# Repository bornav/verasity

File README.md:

# Verasity

Open source tenkeyless keyboard

* Keyboard Maintainer: [Borna Vincek](https://github.com/BornaV)

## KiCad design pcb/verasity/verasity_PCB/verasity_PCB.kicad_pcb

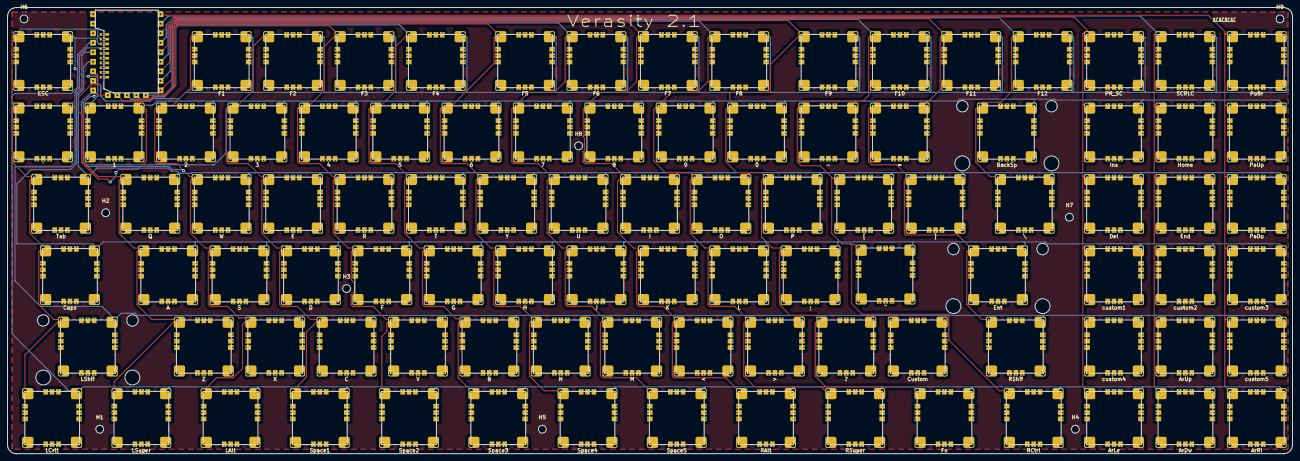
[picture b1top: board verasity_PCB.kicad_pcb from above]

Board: 2 copper layers, 342.9 x 119.1 mm, 107 parts (0 on the bottom side), 23 nets.

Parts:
H1, H2, H3, H4, H5, H6, H7, H8, H9: MountingHole_Pad; MountingHole_2.1mm
U2: ESC; inverse_socket_MX_hotswap
U3: custom1; inverse_socket_MX_hotswap
U4: F1; inverse_socket_MX_hotswap
U5: F2; inverse_socket_MX_hotswap
U6: F3; inverse_socket_MX_hotswap
U7: F4; inverse_socket_MX_hotswap
U8: F5; inverse_socket_MX_hotswap
U9: F6; inverse_socket_MX_hotswap
U10: F7; inverse_socket_MX_hotswap
U11: F8; inverse_socket_MX_hotswap
U12: F9; inverse_socket_MX_hotswap
U13: F10; inverse_socket_MX_hotswap
U14: F11; inverse_socket_MX_hotswap
U15: F12; inverse_socket_MX_hotswap
U16: PR_SC; inverse_socket_MX_hotswap
U17: SCRLC; inverse_socket_MX_hotswap
U18: PoBr; inverse_socket_MX_hotswap
U19: `; inverse_socket_MX_hotswap
U20: 1; inverse_socket_MX_hotswap
U21: 2; inverse_socket_MX_hotswap
U22: 3; inverse_socket_MX_hotswap
U23: 4; inverse_socket_MX_hotswap
U24: 5; inverse_socket_MX_hotswap
U25: 6; inverse_socket_MX_hotswap
U26: 7; inverse_socket_MX_hotswap
U27: 8; inverse_socket_MX_hotswap
U28: 9; inverse_socket_MX_hotswap
U29: 0; inverse_socket_MX_hotswap
U30: -; inverse_socket_MX_hotswap
U31: =; inverse_socket_MX_hotswap
U32: BackSp; inverse_socket_MX_hotswap_2.5U_stabilizers
U33: Ins; inverse_socket_MX_hotswap
U34: Home; inverse_socket_MX_hotswap
U35: PaUp; inverse_socket_MX_hotswap
U36: Tab; inverse_socket_MX_hotswap
U37: Q; inverse_socket_MX_hotswap
U38: W; inverse_socket_MX_hotswap
U39: E; inverse_socket_MX_hotswap
U40: R; inverse_socket_MX_hotswap
U41: T; inverse_socket_MX_hotswap
U42: Y; inverse_socket_MX_hotswap
U43: U; inverse_socket_MX_hotswap
U44: I; inverse_socket_MX_hotswap
U45: O; inverse_socket_MX_hotswap
U46: P; inverse_socket_MX_hotswap
U47: [; inverse_socket_MX_hotswap
U48: ]; inverse_socket_MX_hotswap
U49: \; inverse_socket_MX_hotswap
U50: Del; inverse_socket_MX_hotswap
U51: End; inverse_socket_MX_hotswap
U52: PaDo; inverse_socket_MX_hotswap
U53: Caps; inverse_socket_MX_hotswap
U54: A; inverse_socket_MX_hotswap
U55: S; inverse_socket_MX_hotswap
U56: D; inverse_socket_MX_hotswap
U57: F; inverse_socket_MX_hotswap
U58: G; inverse_socket_MX_hotswap
U59: H; inverse_socket_MX_hotswap
U60: J; inverse_socket_MX_hotswap
U61: K; inverse_socket_MX_hotswap
U62: L; inverse_socket_MX_hotswap
U63: ;; inverse_socket_MX_hotswap
U64: "; inverse_socket_MX_hotswap
U65: Ent; inverse_socket_MX_hotswap_2.5U_stabilizers
U66: LShif; inverse_socket_MX_hotswap_2.5U_stabilizers
U67: Z; inverse_socket_MX_hotswap
U68: X; inverse_socket_MX_hotswap
U69: C; inverse_socket_MX_hotswap
U70: V; inverse_socket_MX_hotswap
U71: B; inverse_socket_MX_hotswap
U72: N; inverse_socket_MX_hotswap
U73: M; inverse_socket_MX_hotswap
U74: <; inverse_socket_MX_hotswap
U75: >; inverse_socket_MX_hotswap
U76: ?; inverse_socket_MX_hotswap
U77: Custom; inverse_socket_MX_hotswap
U78: RShif; inverse_socket_MX_hotswap
U79: ArUp; inverse_socket_MX_hotswap
U80: LCrtl; inverse_socket_MX_hotswap
U81: LSuper; inverse_socket_MX_hotswap
U82: LAlt; inverse_socket_MX_hotswap
U83: Space1; inverse_socket_MX_hotswap
U84: Space2; inverse_socket_MX_hotswap
U85: Space3; inverse_socket_MX_hotswap
U86: Space4; inverse_socket_MX_hotswap
U87: Space5; inverse_socket_MX_hotswap
U88: custom2; inverse_socket_MX_hotswap
U89: RAlt; inverse_socket_MX_hotswap
U90: RSuper; inverse_socket_MX_hotswap
U91: Fn; inverse_socket_MX_hotswap
U92: RCtrl; inverse_socket_MX_hotswap
U93: ArLe; inverse_socket_MX_hotswap
U94: ArDw; inverse_socket_MX_hotswap
U95: ArRi; inverse_socket_MX_hotswap
U96: custom3; inverse_socket_MX_hotswap
U97: custom4; inverse_socket_MX_hotswap
U98: custom5; inverse_socket_MX_hotswap
U99: RP2040; waveshare-rp2040-pad_solder_with_cutout

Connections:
COL1: U2.1 (COL), U19.1 (COL), U36.1 (COL), U53.1 (COL), U66.1 (COL), U80.1 (COL), U99.37 (GPIO25)
COL2: U20.1 (COL), U37.1 (COL), U54.1 (COL), U67.1 (COL), U81.1 (COL), U99.18 (GPIO15)
COL3: U4.1 (COL), U21.1 (COL), U38.1 (COL), U55.1 (COL), U68.1 (COL), U82.1 (COL), U99.17 (GPIO14)
COL4: U5.1 (COL), U22.1 (COL), U39.1 (COL), U56.1 (COL), U69.1 (COL), U83.1 (COL), U99.16 (GPIO13)
COL5: U6.1 (COL), U23.1 (COL), U40.1 (COL), U57.1 (COL), U70.1 (COL), U84.1 (COL), U99.15 (GPIO12)
COL6: U7.1 (COL), U24.1 (COL), U41.1 (COL), U58.1 (COL), U71.1 (COL), U85.1 (COL), U99.14 (GPIO11)
COL7: U8.1 (COL), U25.1 (COL), U42.1 (COL), U59.1 (COL), U72.1 (COL), U86.1 (COL), U99.13 (GPIO10)
COL8: U9.1 (COL), U26.1 (COL), U43.1 (COL), U60.1 (COL), U73.1 (COL), U87.1 (COL), U99.12 (GPIO9)
COL9: U10.1 (COL), U27.1 (COL), U44.1 (COL), U61.1 (COL), U74.1 (COL), U89.1 (COL), U99.11 (GPIO8)
COL10: U11.1 (COL), U28.1 (COL), U45.1 (COL), U62.1 (COL), U75.1 (COL), U90.1 (COL), U99.9 (GPIO7)
COL11: U12.1 (COL), U29.1 (COL), U46.1 (COL), U63.1 (COL), U76.1 (COL), U91.1 (COL), U99.8 (GPIO6)
COL12: U13.1 (COL), U30.1 (COL), U47.1 (COL), U64.1 (COL), U77.1 (COL), U92.1 (COL), U99.7 (GPIO5)
COL13: U14.1 (COL), U31.1 (COL), U48.1 (COL), U65.1 (COL), U78.1 (COL), U99.6 (GPIO4)
COL14: U15.1 (COL), U32.1 (COL), U49.1 (COL), U99.5 (GPIO3)
COL15: U3.1 (COL), U16.1 (COL), U33.1 (COL), U50.1 (COL), U93.1 (COL), U97.1 (COL), U99.4 (GPIO2)
COL16: U17.1 (COL), U34.1 (COL), U51.1 (COL), U79.1 (COL), U88.1 (COL), U94.1 (COL), U99.3 (GPIO1)
COL17: U18.1 (COL), U35.1 (COL), U52.1 (COL), U95.1 (COL), U96.1 (COL), U98.1 (COL), U99.2 (GPIO0)
ROW1: U2.2 (ROW), U4.2 (ROW), U5.2 (ROW), U6.2 (ROW), U7.2 (ROW), U8.2 (ROW), U9.2 (ROW), U10.2 (ROW), U11.2 (ROW), U12.2 (ROW), U13.2 (ROW), U14.2 (ROW), U15.2 (ROW), U16.2 (ROW), U17.2 (ROW), U18.2 (ROW), U99.36 (GPIO24)
ROW2: U19.2 (ROW), U20.2 (ROW), U21.2 (ROW), U22.2 (ROW), U23.2 (ROW), U24.2 (ROW), U25.2 (ROW), U26.2 (ROW), U27.2 (ROW), U28.2 (ROW), U29.2 (ROW), U30.2 (ROW), U31.2 (ROW), U32.2 (ROW), U33.2 (ROW), U34.2 (ROW), U35.2 (ROW), U99.38 (GPIO26_ADC0)
ROW3: U36.2 (ROW), U37.2 (ROW), U38.2 (ROW), U39.2 (ROW), U40.2 (ROW), U41.2 (ROW), U42.2 (ROW), U43.2 (ROW), U44.2 (ROW), U45.2 (ROW), U46.2 (ROW), U47.2 (ROW), U48.2 (ROW), U49.2 (ROW), U50.2 (ROW), U51.2 (ROW), U52.2 (ROW), U99.39 (GPIO27_ADC1)
ROW4: U3.2 (ROW), U53.2 (ROW), U54.2 (ROW), U55.2 (ROW), U56.2 (ROW), U57.2 (ROW), U58.2 (ROW), U59.2 (ROW), U60.2 (ROW), U61.2 (ROW), U62.2 (ROW), U63.2 (ROW), U64.2 (ROW), U65.2 (ROW), U88.2 (ROW), U96.2 (ROW), U99.40 (GPIO28_ADC2)
ROW5: U66.2 (ROW), U67.2 (ROW), U68.2 (ROW), U69.2 (ROW), U70.2 (ROW), U71.2 (ROW), U72.2 (ROW), U73.2 (ROW), U74.2 (ROW), U75.2 (ROW), U76.2 (ROW), U77.2 (ROW), U78.2 (ROW), U79.2 (ROW), U97.2 (ROW), U98.2 (ROW), U99.35 (GPIO23)
ROW6: U80.2 (ROW), U81.2 (ROW), U82.2 (ROW), U83.2 (ROW), U84.2 (ROW), U85.2 (ROW), U86.2 (ROW), U87.2 (ROW), U89.2 (ROW), U90.2 (ROW), U91.2 (ROW), U92.2 (ROW), U93.2 (ROW), U94.2 (ROW), U95.2 (ROW), U99.41 (GPIO29_ADC3)

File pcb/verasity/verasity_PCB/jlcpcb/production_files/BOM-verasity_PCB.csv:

Comment,Designator,Footprint,LCSC
RP2040,U99,waveshare-rp2040-pad_solder_with_cutout,C5350143
F3,U6,inverse_socket_MX_hotswap,
5,U24,inverse_socket_MX_hotswap,
;,U63,inverse_socket_MX_hotswap,
ArUp,U79,inverse_socket_MX_hotswap,
?,U76,inverse_socket_MX_hotswap,
LAlt,U82,inverse_socket_MX_hotswap,
I,U44,inverse_socket_MX_hotswap,
RSuper,U90,inverse_socket_MX_hotswap,
F12,U15,inverse_socket_MX_hotswap,
`,U19,inverse_socket_MX_hotswap,
Home,U34,inverse_socket_MX_hotswap,
Ent,U65,inverse_socket_MX_hotswap_2.5U_stabilizers,
F8,U11,inverse_socket_MX_hotswap,
Fn,U91,inverse_socket_MX_hotswap,
E,U39,inverse_socket_MX_hotswap,
RCtrl,U92,inverse_socket_MX_hotswap,
3,U22,inverse_socket_MX_hotswap,
S,U55,inverse_socket_MX_hotswap,
F4,U7,inverse_socket_MX_hotswap,
=,U31,inverse_socket_MX_hotswap,
MountingHole_Pad,H8,MountingHole_2.1mm,
MountingHole_Pad,H6,MountingHole_2.1mm,
F9,U12,inverse_socket_MX_hotswap,
Ins,U33,inverse_socket_MX_hotswap,
Space4,U86,inverse_socket_MX_hotswap,
],U48,inverse_socket_MX_hotswap,
LCrtl,U80,inverse_socket_MX_hotswap,
custom5,U98,inverse_socket_MX_hotswap,
MountingHole_Pad,H2,MountingHole_2.1mm,
\,U49,inverse_socket_MX_hotswap,
C,U69,inverse_socket_MX_hotswap,
X,U68,inverse_socket_MX_hotswap,
7,U26,inverse_socket_MX_hotswap,
>,U75,inverse_socket_MX_hotswap,
K,U61,inverse_socket_MX_hotswap,
2,U21,inverse_socket_MX_hotswap,
Del,U50,inverse_socket_MX_hotswap,
O,U45,inverse_socket_MX_hotswap,
T,U41,inverse_socket_MX_hotswap,
MountingHole_Pad,H1,MountingHole_2.1mm,
Caps,U53,inverse_socket_MX_hotswap,
8,U27,inverse_socket_MX_hotswap,
4,U23,inverse_socket_MX_hotswap,
MountingHole_Pad,H7,MountingHole_2.1mm,
PaUp,U35,inverse_socket_MX_hotswap,
Space5,U87,inverse_socket_MX_hotswap,
F1,U4,inverse_socket_MX_hotswap,
J,U60,inverse_socket_MX_hotswap,
PR_SC,U16,inverse_socket_MX_hotswap,
G,U58,inverse_socket_MX_hotswap,
P,U46,inverse_socket_MX_hotswap,
Tab,U36,inverse_socket_MX_hotswap,
ArDw,U94,inverse_socket_MX_hotswap,
R,U40,inverse_socket_MX_hotswap,
custom1,U3,inverse_socket_MX_hotswap,
6,U25,inverse_socket_MX_hotswap,
U,U43,inverse_socket_MX_hotswap,
H,U59,inverse_socket_MX_hotswap,
F,U57,inverse_socket_MX_hotswap,
SCRLC,U17,inverse_socket_MX_hotswap,
Space1,U83,inverse_socket_MX_hotswap,
D,U56,inverse_socket_MX_hotswap,
1,U20,inverse_socket_MX_hotswap,
RAlt,U89,inverse_socket_MX_hotswap,
-,U30,inverse_socket_MX_hotswap,
LShif,U66,inverse_socket_MX_hotswap_2.5U_stabilizers,
Space3,U85,inverse_socket_MX_hotswap,
BackSp,U32,inverse_socket_MX_hotswap_2.5U_stabilizers,
Z,U67,inverse_socket_MX_hotswap,
PoBr,U18,inverse_socket_MX_hotswap,
Space2,U84,inverse_socket_MX_hotswap,
F11,U14,inverse_socket_MX_hotswap,
LSuper,U81,inverse_socket_MX_hotswap,
<,U74,inverse_socket_MX_hotswap,
custom2,U88,inverse_socket_MX_hotswap,
End,U51,inverse_socket_MX_hotswap,
F10,U13,inverse_socket_MX_hotswap,
MountingHole_Pad,H5,MountingHole_2.1mm,
9,U28,inverse_socket_MX_hotswap,
MountingHole_Pad,H9,MountingHole_2.1mm,
F7,U10,inverse_socket_MX_hotswap,
custom3,U96,inverse_socket_MX_hotswap,
MountingHole_Pad,H3,MountingHole_2.1mm,
ArRi,U95,inverse_socket_MX_hotswap,
ESC,U2,inverse_socket_MX_hotswap,
A,U54,inverse_socket_MX_hotswap,
V,U70,inverse_socket_MX_hotswap,
F5,U8,inverse_socket_MX_hotswap,
0,U29,inverse_socket_MX_hotswap,
PaDo,U52,inverse_socket_MX_hotswap,
MountingHole_Pad,H4,MountingHole_2.1mm,
F2,U5,inverse_socket_MX_hotswap,
RShif,U78,inverse_socket_MX_hotswap,
Q,U37,inverse_socket_MX_hotswap,
custom4,U97,inverse_socket_MX_hotswap,
Custom,U77,inverse_socket_MX_hotswap,
Y,U42,inverse_socket_MX_hotswap,
B,U71,inverse_socket_MX_hotswap,
[,U47,inverse_socket_MX_hotswap,
"""",U64,inverse_socket_MX_hotswap,
W,U38,inverse_socket_MX_hotswap,
N,U72,inverse_socket_MX_hotswap,
F6,U9,inverse_socket_MX_hotswap,
L,U62,inverse_socket_MX_hotswap,
ArLe,U93,inverse_socket_MX_hotswap,
M,U73,inverse_socket_MX_hotswap,

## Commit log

2021-10-17 contex
2021-10-17 contex2
2021-11-20 upgrades
2021-11-20 removed info.json unnecessary
2021-11-20 new layout
2023-04-03 UNTESTED!!!
2023-05-08 verasity 2.0
2023-05-13 prerelease
2023-06-01 one used for prod
2023-06-08 new 2.1 prod
2023-06-22 added qmk configuration for the board
